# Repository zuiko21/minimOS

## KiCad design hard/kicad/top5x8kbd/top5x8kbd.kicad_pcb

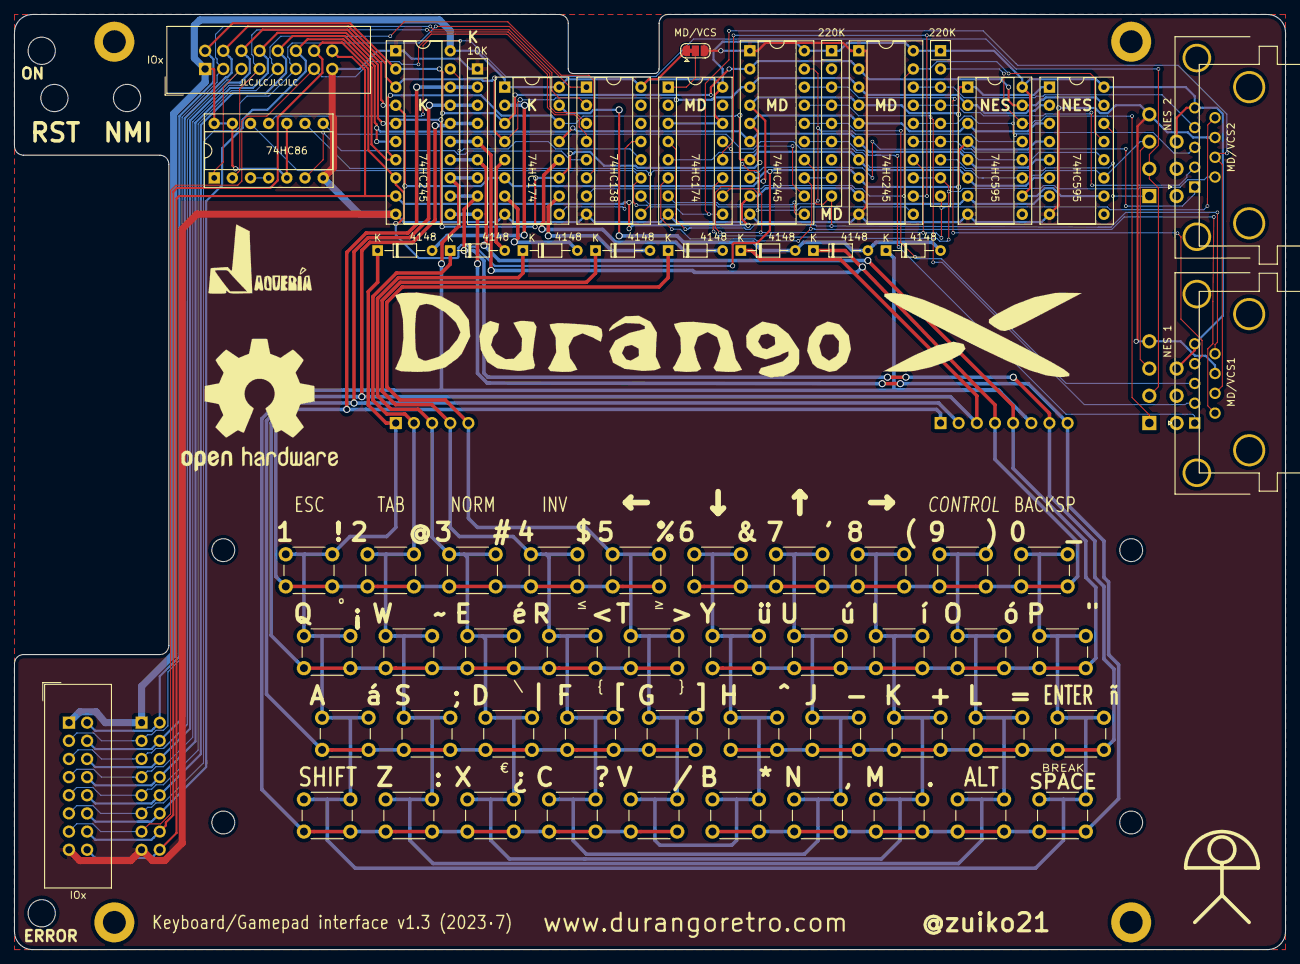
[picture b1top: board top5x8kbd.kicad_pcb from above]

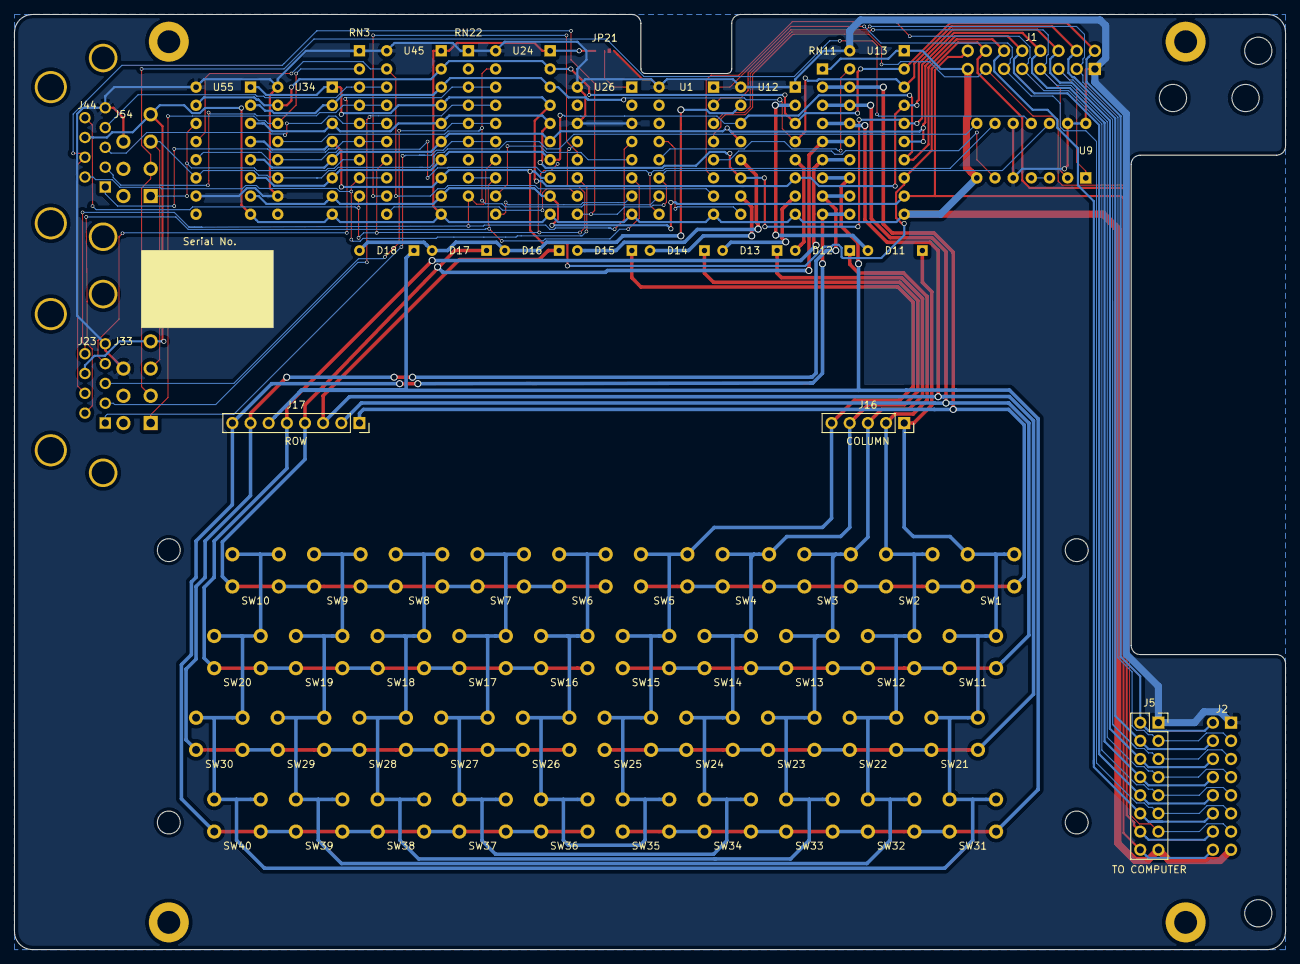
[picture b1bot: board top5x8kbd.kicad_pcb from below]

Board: 2 copper layers, 177.8 x 130.8 mm, 81 parts (3 on the bottom side), 64 nets.

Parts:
D11, D12, D13, D14, D15, D16, D17, D18: 4148; D_DO-34_SOD68_P7.62mm_Horizontal
H1: RST; MountingHole_3.2mm_M3_DIN965_Pad
H2: NMI; MountingHole_3.2mm_M3_DIN965_Pad
H3, H4: MountingHole_3.2mm_M3_DIN965_Pad
H5, H6, H7, H8: MountingHole_3.2mm_M3_DIN965
J1, J2: IOx; IDC-Header_2x08_P2.54mm_Vertical
J5: TO COMPUTER; PinSocket_2x08_P2.54mm_Vertical
J16: COLUMN; PinSocket_1x05_P2.54mm_Vertical
J17: ROW; PinSocket_1x08_P2.54mm_Vertical
J23: MD/VCS1; DSUB-9_Male_Horizontal_P2.77x2.84mm_EdgePinOffset4.94mm_Hou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
J33: NES 1; NES gamepad
J44: MD/VCS2; DSUB-9_Male_Horizontal_P2.77x2.84mm_EdgePinOffset4.94mm_Hou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
J54: NES 2; NES gamepad
JP21: MD/VCS; SolderJumper-3_P1.3mm_Bridged12_RoundedPad1.0x1.5mm
LOGO1: OSHW-Logo2_24.3x20mm_SilkScreen
LOGO2: durango-x18
LOGO3: jaqueria
RN3, RN22: 220K; R_Array_SIP9
RN11: 10K; R_Array_SIP9
SW1: 1 !; SW_PUSH_6mm
SW2: 2 @; SW_PUSH_6mm
SW3: 3 #; SW_PUSH_6mm
SW4: 4 $; SW_PUSH_6mm
SW5: 5 %; SW_PUSH_6mm
SW6: 6 &; SW_PUSH_6mm
SW7: 7 '; SW_PUSH_6mm
SW8: 8 (; SW_PUSH_6mm
SW9: 9 ); SW_PUSH_6mm
SW10: 0 _; SW_PUSH_6mm
SW11: Q ¡; SW_PUSH_6mm
SW12: W ~~; SW_PUSH_6mm
SW13: E é; SW_PUSH_6mm
SW14: R <; SW_PUSH_6mm
SW15: T >; SW_PUSH_6mm
SW16: Y ü; SW_PUSH_6mm
SW17: U ú; SW_PUSH_6mm
SW18: I í; SW_PUSH_6mm
SW19: O ó; SW_PUSH_6mm
SW20: P "; SW_PUSH_6mm
SW21: A á; SW_PUSH_6mm
SW22: S ;; SW_PUSH_6mm
SW23: D |; SW_PUSH_6mm
SW24: F [; SW_PUSH_6mm
SW25: G ]; SW_PUSH_6mm
SW26: H ^; SW_PUSH_6mm
SW27: J -; SW_PUSH_6mm
SW28: K +; SW_PUSH_6mm
SW29: L =; SW_PUSH_6mm
SW30: ENTER ñ; SW_PUSH_6mm
SW31: SHIFT; SW_PUSH_6mm
SW32: Z :; SW_PUSH_6mm
SW33: X ¿; SW_PUSH_6mm
SW34: C ?; SW_PUSH_6mm
SW35: V /; SW_PUSH_6mm
SW36: B *; SW_PUSH_6mm
SW37: N ,; SW_PUSH_6mm
SW38: M .; SW_PUSH_6mm
SW39: ALT; SW_PUSH_6mm
SW40: SPACE; SW_PUSH_6mm
U1: 74HC138; DIP-16_W7.62mm_Socket
U9: 74HC86; DIP-14_W7.62mm_Socket
U12, U26: 74HC174; DIP-16_W7.62mm_Socket
U13, U24, U45: 74HC245; DIP-20_W7.62mm_Socket
U34, U55: 74HC595; DIP-16_W7.62mm_Socket

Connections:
+5V: J1.1, J2.1, J5.1, J23.5, J33.6, J44.5, J54.6, JP21.1, RN3.1, RN22.1, U1.16, U9.5, U9.10, U9.13, U9.14, U12.1, U12.16, U13.20, U24.20, U26.3, U26.14, U26.16, U34.10, U34.16, U45.20, U55.10, U55.16
/BR~W: J1.11, J2.11, J5.11, U1.1
/C1: D11.2, U12.2
/C2: D12.2, U12.5
/C3: D13.2, U12.7
/C4: D14.2, U12.10
/C5: D15.2, U12.12
/ID: D16.2, D17.2, D18.2, U12.15
/K~OE: U1.12, U13.19
/LATCH: J33.3, J54.3, U9.11
/NCLK: J33.5, J54.5, U9.8, U34.11, U55.11
/P1~OE: U1.10, U24.19, U34.13
/P2~OE: U1.7, U45.19, U55.13
/SEL: U9.3, U9.4
/VCS: JP21.2, U26.1
/~A1: U24.11, U26.7
/~A2: U26.10, U45.11
/~AB1: J23.6, RN22.8, U24.13, U26.6
/~AB2: J44.6, RN3.8, U26.11, U45.13
/~CSEL: U1.13, U12.9
/~DAT1: J33.1, RN3.2, U34.14
/~DAT2: J54.1, RN3.7, U55.14
/~DN1: J23.2, RN22.4, U24.17
/~DN2: J44.2, RN3.4, U45.17
/~IOX: J1.13, J2.13, J5.13, U1.4
/~LATCH: J23.7, J44.7, U1.11, U9.12, U26.9
/~LT1: J23.3, RN22.5, U24.16
/~LT2: J44.3, RN3.5, U45.16
/~NCLK: U1.9, U9.9, U34.12, U55.12
/~RT1: J23.4, RN22.3, U24.18
/~RT2: J44.4, RN3.3, U45.18
/~S1: U24.12, U26.5
/~S2: U26.12, U45.12
/~SC1: J23.9, RN22.9, U24.14, U26.4
/~SC2: J44.9, RN3.9, U26.13, U45.14
/~SEL: U1.5, U9.6
/~UP1: J23.1, RN22.6, U24.15
/~UP2: J44.1, RN3.6, U45.15
BA0: J1.3, J2.3, J5.3, U1.2
BA1: J1.5, J2.5, J5.5, U9.1
BA2: J1.7, J2.7, J5.7, U1.3, U9.2
BA3: J1.9, J2.9, J5.9, U1.6
COL1: D11.1, J16.1, SW1.2, SW10.2, SW11.2, SW20.2, SW21.2, SW30.2, SW31.2, SW40.2
COL2: D12.1, J16.2, SW2.2, SW9.2, SW12.2, SW19.2, SW22.2, SW29.2, SW32.2, SW39.2
COL3: D13.1, J16.3, SW3.2, SW8.2, SW13.2, SW18.2, SW23.2, SW28.2, SW33.2, SW38.2
COL4: D14.1, J16.4, SW4.2, SW7.2, SW14.2, SW17.2, SW24.2, SW27.2, SW34.2, SW37.2
COL5: D15.1, J16.5, SW5.2, SW6.2, SW15.2, SW16.2, SW25.2, SW26.2, SW35.2, SW36.2
GND: J1.15, J2.15, J5.15, J23.8, J33.7, J44.8, J54.7, JP21.3, RN11.1, U1.8, U9.7, U12.8, U13.1, U13.10, U24.1, U24.10, U26.8, U34.8, U45.1, U45.10, U55.8
PD0: J1.2, J2.2, J5.2, U12.3, U13.2, U24.2, U34.15, U45.2, U55.15
PD1: J1.4, J2.4, J5.4, U12.4, U13.3, U24.3, U34.2, U45.3, U55.2
PD2: J1.6, J2.6, J5.6, U12.6, U13.4, U24.4, U34.1, U45.4, U55.1
PD3: J1.8, J2.8, J5.8, U12.11, U13.5, U24.5, U34.3, U45.5, U55.3
PD4: J1.10, J2.10, J5.10, U12.13, U13.6, U24.6, U34.5, U45.6, U55.5
PD5: J1.12, J2.12, J5.12, U12.14, U13.7, U24.7, U34.6, U45.7, U55.6
PD6: J1.14, J2.14, J5.14, U13.8, U24.8, U34.4, U45.8, U55.4
PD7: J1.16, J2.16, J5.16, U13.9, U24.9, U34.7, U45.9, U55.7
ROW1: J17.1, RN11.2, SW1.1, SW2.1, SW3.1, SW4.1, SW5.1, U13.18
ROW2: J17.2, RN11.3, SW11.1, SW12.1, SW13.1, SW14.1, SW15.1, U13.17
ROW3: D16.1, J17.3, RN11.4, SW21.1, SW22.1, SW23.1, SW24.1, SW25.1, U13.16
ROW4: D17.1, J17.4, RN11.5, SW6.1, SW7.1, SW8.1, SW9.1, SW10.1, U13.15
ROW5: J17.5, RN11.6, SW16.1, SW17.1, SW18.1, SW19.1, SW20.1, U13.14
ROW6: D18.1, J17.6, RN11.7, SW31.1, SW32.1, SW33.1, SW34.1, SW35.1, U13.13
ROW7: J17.7, RN11.8, SW26.1, SW27.1, SW28.1, SW29.1, SW30.1, U13.12
ROW8: J17.8, RN11.9, SW36.1, SW37.1, SW38.1, SW39.1, SW40.1, U13.11

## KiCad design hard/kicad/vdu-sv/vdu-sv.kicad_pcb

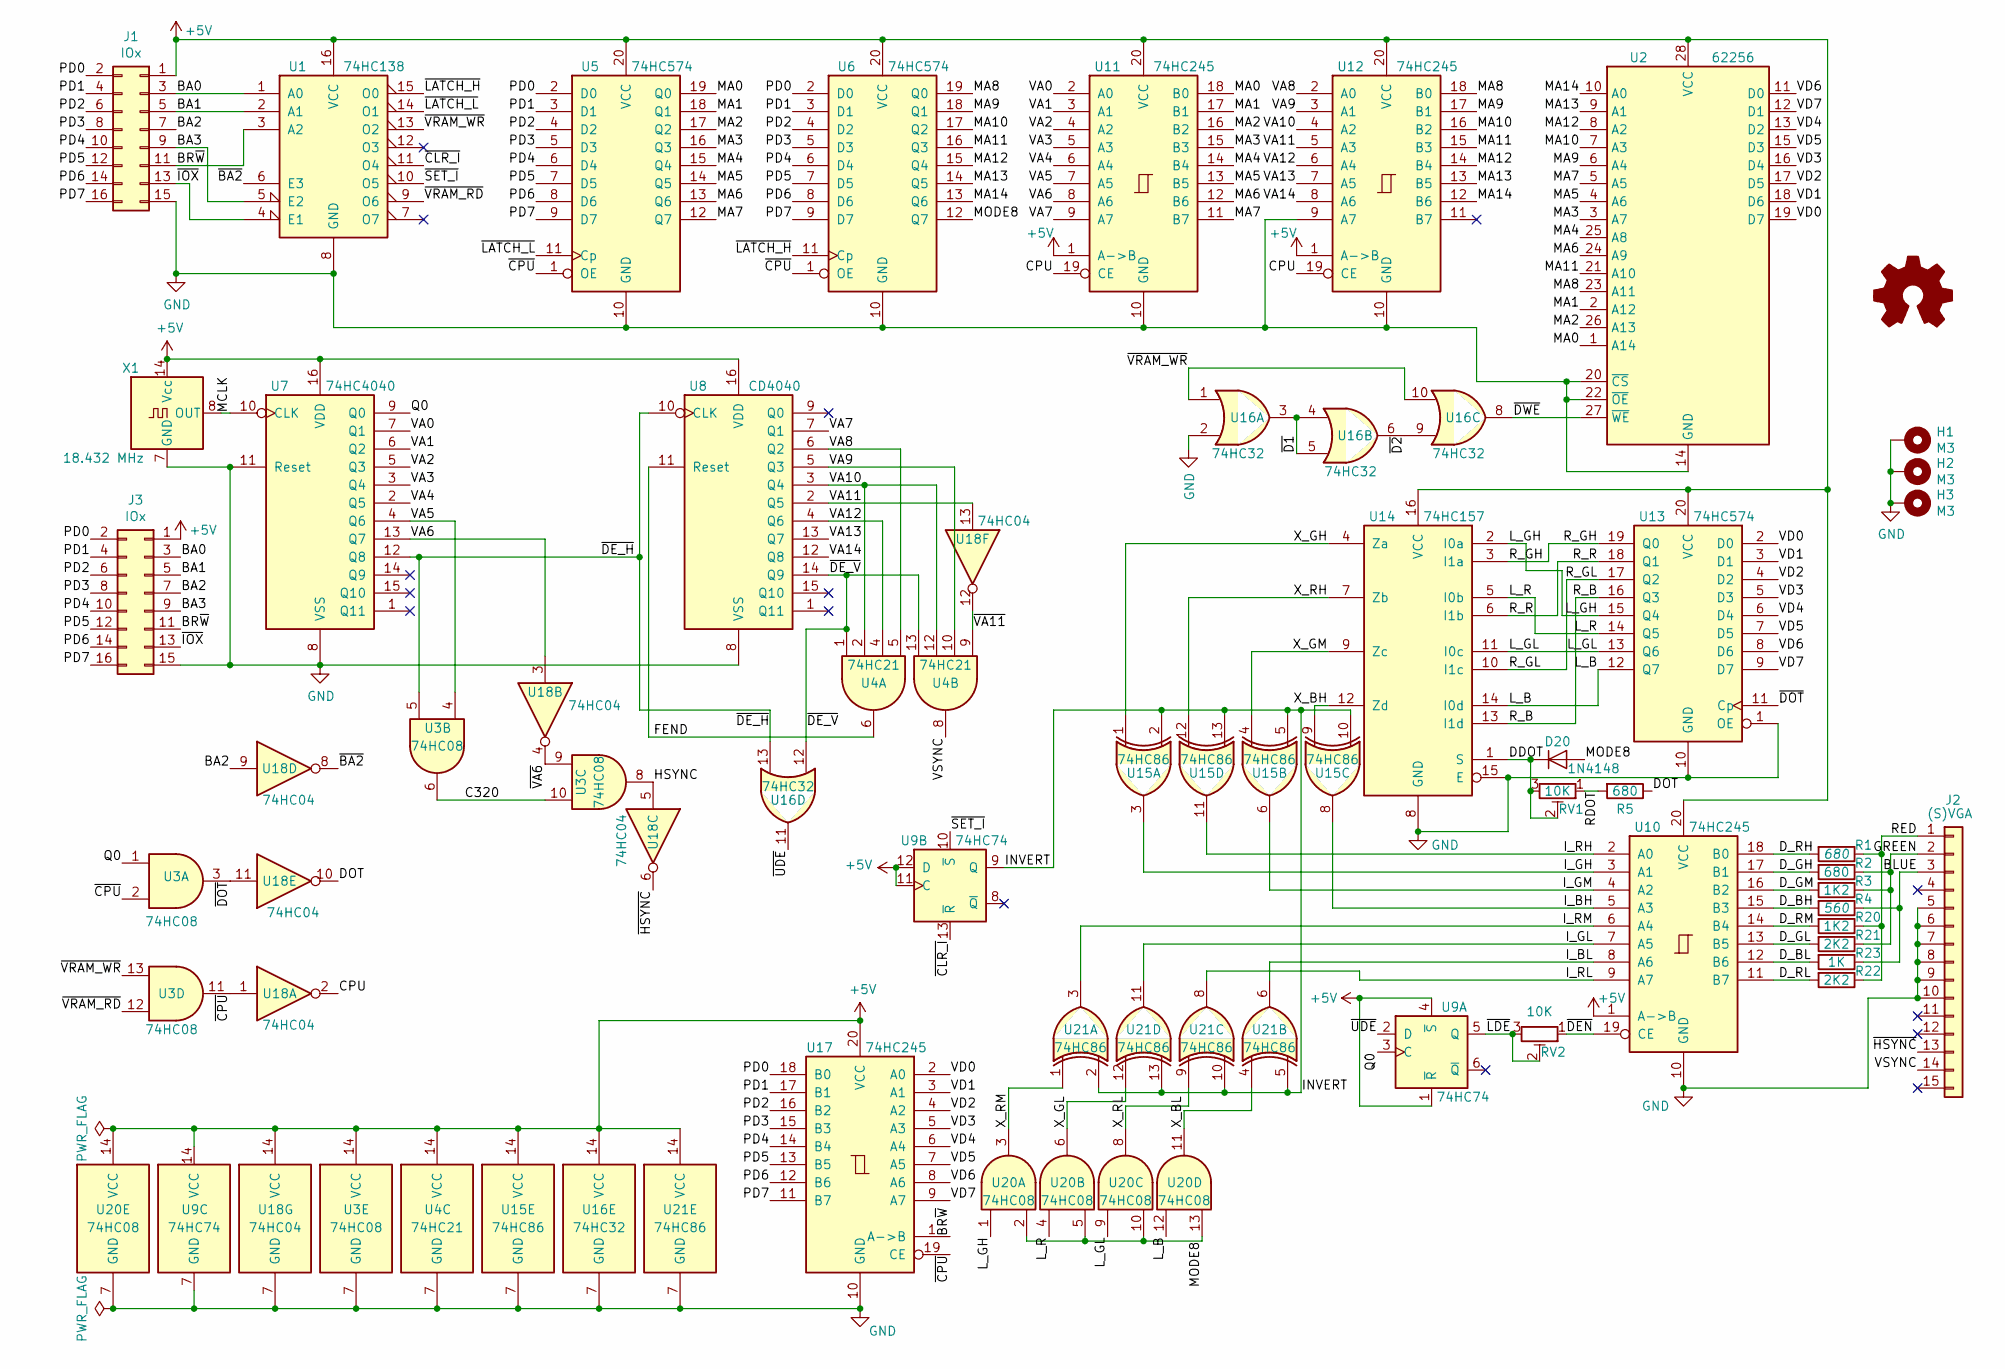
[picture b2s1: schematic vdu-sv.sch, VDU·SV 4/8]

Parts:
D20: 1N4148; D_DO-35_SOD27_P2.54mm_Vertical_AnodeUp
H1, H2, H3: M3; MountingHole_3.2mm_M3_DIN965_Pad
J1: IOx; PinSocket_2x08_P2.54mm_Horizontal
J2: (S)VGA; DSUB-15-HD_Female_Horizontal_P2.29x1.98mm_EdgePinOffset3.03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
J3: IOx; IDC-Header_2x08_P2.54mm_Vertical
LOGO1: La Jaquería; jaqueria
R1, R2, R5: 680; R_Axial_DIN0207_L6.3mm_D2.5mm_P2.54mm_Vertical
R3, R20: 1K2; R_Axial_DIN0207_L6.3mm_D2.5mm_P2.54mm_Vertical
R4: 560; R_Axial_DIN0207_L6.3mm_D2.5mm_P2.54mm_Vertical
R21, R22: 2K2; R_Axial_DIN0207_L6.3mm_D2.5mm_P2.54mm_Vertical
R23: 1K; R_Axial_DIN0207_L6.3mm_D2.5mm_P2.54mm_Vertical
RV1, RV2: 10K; Potentiometer_Piher_PT-6-V_Vertical
U1: 74HC138; DIP-16_W7.62mm_Socket
U2: 62256; DIP-28_W7.62mm_Socket
U3, U20: 74HC08; DIP-14_W7.62mm_Socket
U4: 74HC21; DIP-14_W7.62mm_Socket
U5, U6, U13: 74HC574; DIP-20_W7.62mm_Socket
U7: 74HC4040; DIP-16_W7.62mm_Socket
U8: CD4040; DIP-16_W7.62mm_Socket
U9: 74HC74; DIP-14_W7.62mm_Socket
U10, U11, U12, U17: 74HC245; DIP-20_W7.62mm_Socket
U14: 74HC157; DIP-16_W7.62mm_Socket
U15, U21: 74HC86; DIP-14_W7.62mm_Socket
U16: 74HC32; DIP-14_W7.62mm_Socket
U18: 74HC04; DIP-14_W7.62mm_Socket
X1: 18.432 MHz; Oscillator_DIP-14

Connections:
+5V: J1.1, J3.1, U1.16 (VCC), U2.28 (VCC), U3.14 (VCC), U4.14 (VCC), U5.20 (VCC), U6.20 (VCC), U7.16 (VDD), U8.16 (VDD), U9.1 (~R), U9.4 (~S), U9.11 (C), U9.12 (D), U9.14 (VCC), U10.1 (A->B), U10.20 (VCC), U11.1 (A->B), U11.20 (VCC), U12.1 (A->B), U12.20 (VCC), U13.20 (VCC), U14.16 (VCC), U15.14 (VCC), U16.14 (VCC), U17.20 (VCC), U18.14 (VCC), U20.14 (VCC), U21.14 (VCC), X1.14 (Vcc)
/BA0: J1.3, J3.3, U1.1 (A0)
/BA1: J1.5, J3.5, U1.2 (A1)
/BA2: J1.7, J3.7, U18.9
/BA3: J1.9, J3.9, U1.5 (E2)
/BLUE: J2.3, R4.1, R23.1
/BR~W: J1.11, J3.11, U1.3 (A2), U17.1 (A->B)
/C320: U3.6, U3.10
/CPU: U11.19 (CE), U12.19 (CE), U18.2
/DDOT: D20.1 (K), RV1.2, RV1.3, U14.1 (S)
/DOT: R5.1, U18.10
/D_BH: R4.2, U10.15 (B3)
/D_BL: R23.2, U10.12 (B6)
/D_GH: R2.2, U10.17 (B1)
/D_GL: R21.2, U10.13 (B5)
/D_GM: R3.2, U10.16 (B2)
/D_RH: R1.2, U10.18 (B0)
/D_RL: R22.2, U10.11 (B7)
/D_RM: R20.2, U10.14 (B4)
/FEND: U4.6, U8.11 (Reset)
/GREEN: J2.2, R2.1, R3.1, R21.1
/HSYNC: U3.8, U18.5
/INVERT: U9.9 (Q), U15.2, U15.5, U15.10, U15.13, U21.2, U21.5, U21.10, U21.13
/I_BH: U10.5 (A3), U15.8
/I_BL: U10.8 (A6), U21.6
/I_GH: U10.3 (A1), U15.3
/I_GL: U10.7 (A5), U21.11
/I_GM: U10.4 (A2), U15.6
/I_RH: U10.2 (A0), U15.11
/I_RL: U10.9 (A7), U21.8
/I_RM: U10.6 (A4), U21.3
/L_B: U13.12 (Q7), U14.14 (I0d), U20.12
/L_GH: U13.15 (Q4), U14.2 (I0a), U20.1
/L_GL: U13.13 (Q6), U14.11 (I0c), U20.9
/L_R: U13.14 (Q5), U14.5 (I0b), U20.4
/MA0: U2.1 (A14), U5.19 (Q0), U11.18 (B0)
/MA1: U2.2 (A12), U5.18 (Q1), U11.17 (B1)
/MA2: U2.26 (A13), U5.17 (Q2), U11.16 (B2)
/MA3: U2.3 (A7), U5.16 (Q3), U11.15 (B3)
/MA4: U2.25 (A8), U5.15 (Q4), U11.14 (B4)
/MA5: U2.4 (A6), U5.14 (Q5), U11.13 (B5)
/MA6: U2.24 (A9), U5.13 (Q6), U11.12 (B6)
/MA7: U2.5 (A5), U5.12 (Q7), U11.11 (B7)
/MA8: U2.23 (A11), U6.19 (Q0), U12.18 (B0)
/MA9: U2.6 (A4), U6.18 (Q1), U12.17 (B1)
/MA10: U2.7 (A3), U6.17 (Q2), U12.16 (B2)
/MA11: U2.21 (A10), U6.16 (Q3), U12.15 (B3)
/MA12: U2.8 (A2), U6.15 (Q4), U12.14 (B4)
/MA13: U2.9 (A1), U6.14 (Q5), U12.13 (B5)
/MA14: U2.10 (A0), U6.13 (Q6), U12.12 (B6)
/MCLK: U7.10 (CLK), X1.8 (OUT)
/MODE8: D20.2 (A), U6.12 (Q7), U20.2, U20.5, U20.10, U20.13
/PD0: J1.2, J3.2, U5.2 (D0), U6.2 (D0), U17.18 (B0)
/PD1: J1.4, J3.4, U5.3 (D1), U6.3 (D1), U17.17 (B1)
/PD2: J1.6, J3.6, U5.4 (D2), U6.4 (D2), U17.16 (B2)
/PD3: J1.8, J3.8, U5.5 (D3), U6.5 (D3), U17.15 (B3)
/PD4: J1.10, J3.10, U5.6 (D4), U6.6 (D4), U17.14 (B4)
/PD5: J1.12, J3.12, U5.7 (D5), U6.7 (D5), U17.13 (B5)
/PD6: J1.14, J3.14, U5.8 (D6), U6.8 (D6), U17.12 (B6)
/PD7: J1.16, J3.16, U5.9 (D7), U6.9 (D7), U17.11 (B7)
/Q0: U3.1, U7.9 (Q0), U9.3 (C)
/RDOT: R5.2, RV1.1
/RED: J2.1, R1.1, R20.1, R22.1
/R_B: U13.16 (Q3), U14.13 (I1d)
/R_GH: U13.19 (Q0), U14.3 (I1a)
/R_GL: U13.17 (Q2), U14.10 (I1c)
/R_R: U13.18 (Q1), U14.6 (I1b)
/VA0: U7.7 (Q1), U11.2 (A0)
/VA1: U7.6 (Q2), U11.3 (A1)
/VA2: U7.5 (Q3), U11.4 (A2)
/VA3: U7.3 (Q4), U11.5 (A3)
/VA4: U7.2 (Q5), U11.6 (A4)
/VA5: U3.4, U7.4 (Q6), U11.7 (A5)
/VA6: U7.13 (Q7), U11.8 (A6), U18.3
/VA7: U8.7 (Q1), U11.9 (A7)
/VA8: U4.5, U8.6 (Q2), U12.2 (A0)
/VA9: U4.10, U8.5 (Q3), U12.3 (A1)
/VA10: U4.2, U4.12, U8.3 (Q4), U12.4 (A2)
/VA11: U8.2 (Q5), U12.5 (A3), U18.13
/VA12: U4.4, U8.4 (Q6), U12.6 (A4)
/VA13: U8.13 (Q7), U12.7 (A5)
/VA14: U8.12 (Q8), U12.8 (A6)
/VD0: U2.19 (D7), U13.2 (D0), U17.2 (A0)
/VD1: U2.18 (D6), U13.3 (D1), U17.3 (A1)
/VD2: U2.17 (D5), U13.4 (D2), U17.4 (A2)
/VD3: U2.16 (D4), U13.5 (D3), U17.5 (A3)
/VD4: U2.13 (D2), U13.6 (D4), U17.6 (A4)
/VD5: U2.15 (D3), U13.7 (D5), U17.7 (A5)
/VD6: U2.11 (D0), U13.8 (D6), U17.8 (A6)
/VD7: U2.12 (D1), U13.9 (D7), U17.9 (A7)
/VSYNC: J2.14, U4.8
/X_BH: U14.12 (Zd), U15.9
/X_BL: U20.11, U21.4
/X_GH: U14.4 (Za), U15.1
/X_GL: U20.6, U21.12
/X_GM: U14.9 (Zc), U15.4
/X_RH: U14.7 (Zb), U15.12
/X_RL: U20.8, U21.9
/X_RM: U20.3, U21.1
/~BA2: U1.6 (E3), U18.8
/~CLR_I: U1.11 (O4), U9.13 (~R)
/~CPU: U3.2, U3.11, U5.1 (OE), U6.1 (OE), U17.19 (CE), U18.1
/~D1: U16.3, U16.4, U16.5
/~D2: U16.6, U16.9
/~DEN: RV2.1, U10.19 (CE)
/~DE_H: U3.5, U7.12 (Q8), U8.10 (CLK), U16.13
/~DE_V: U4.1, U4.13, U8.14 (Q9), U16.12
/~DOT: U3.3, U13.11 (Cp), U18.11
/~DWE: U2.27 (~WE~), U16.8
/~HSYNC: J2.13, U18.6
/~IOX: J1.13, J3.13, U1.4 (E1)
/~LATCH_H: U1.15 (O0), U6.11 (Cp)
/~LATCH_L: U1.14 (O1), U5.11 (Cp)
/~LDE: RV2.2, RV2.3, U9.5 (Q)
/~SET_I: U1.10 (O5), U9.10 (~S)
/~UDE: U9.2 (D), U16.11
/~VA6: U3.9, U18.4
/~VA11: U4.9, U18.12
/~VRAM_RD: U1.9 (O6), U3.12
/~VRAM_WR: U1.13 (O2), U3.13, U16.1, U16.10
GND: H1.1, H2.1, H3.1, J1.15, J2.5, J2.6, J2.7, J2.8, J2.9, J2.10, J3.15, U1.8 (GND), U2.14 (GND), U2.20 (~CS), U2.22 (~OE~), U3.7 (GND), U4.7 (GND), U5.10 (GND), U6.10 (GND), U7.8 (VSS), U7.11 (Reset), U8.8 (VSS), U9.7 (GND), U10.10 (GND), U11.10 (GND), U12.9 (A7), U12.10 (GND), U13.1 (OE), U13.10 (GND), U14.8 (GND), U14.15 (E), U15.7 (GND), U16.2, U16.7 (GND), U17.10 (GND), U18.7 (GND), U20.7 (GND), U21.7 (GND), X1.7 (GND)

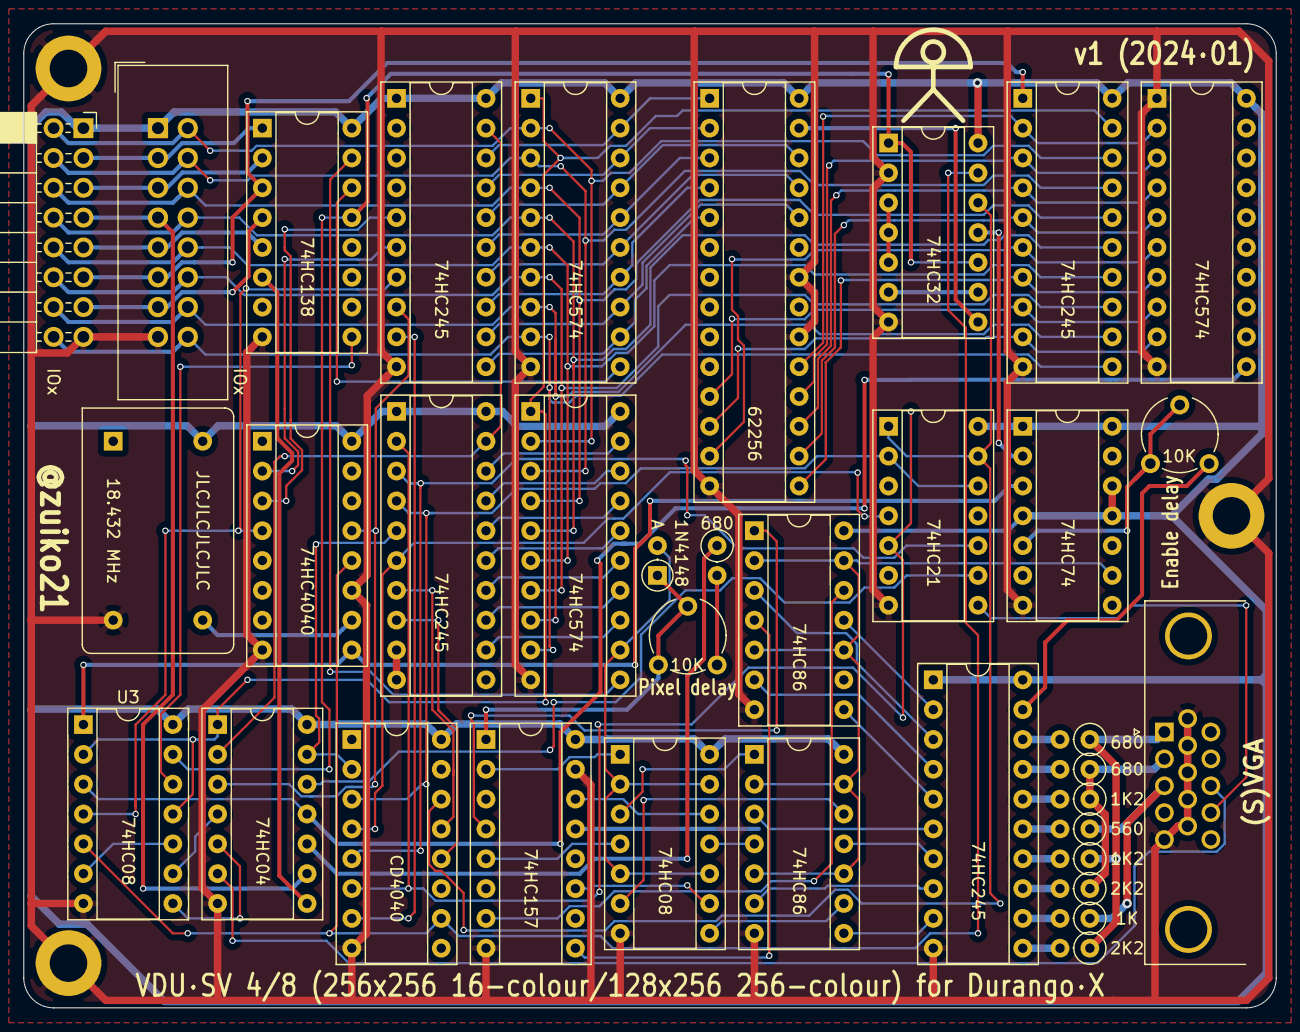
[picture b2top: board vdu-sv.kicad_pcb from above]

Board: 2 copper layers, 106.7 x 83.8 mm, 40 parts (1 on the bottom side), 121 nets.

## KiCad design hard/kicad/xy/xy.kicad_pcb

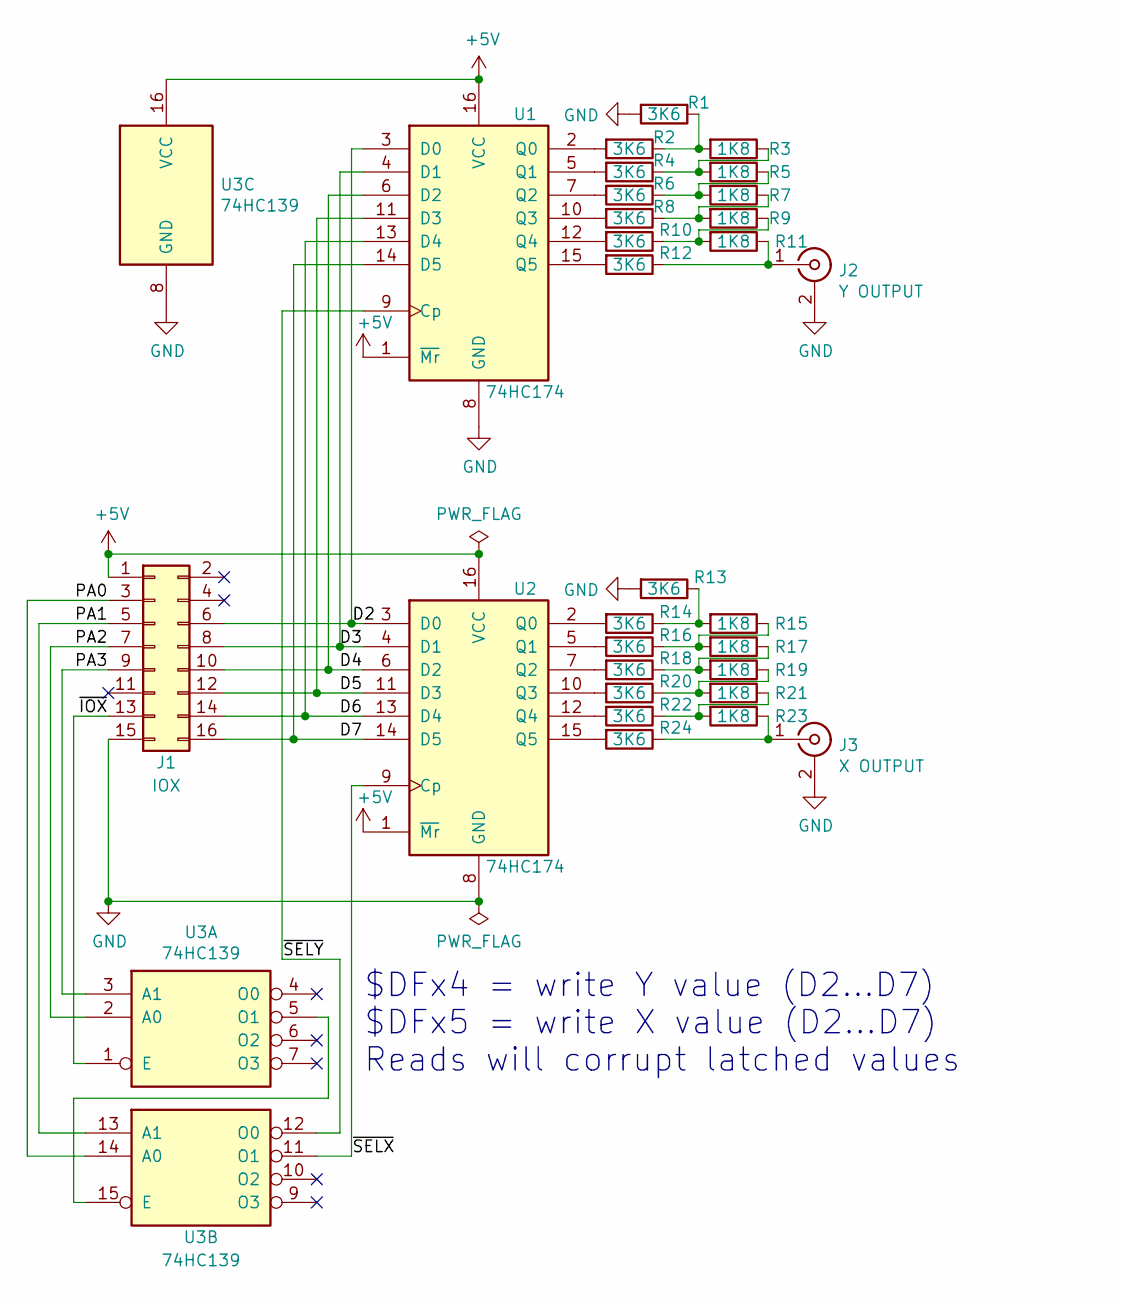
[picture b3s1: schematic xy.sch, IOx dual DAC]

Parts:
J1: IOX; IDC-Header_2x08_P2.54mm_Vertical
J2: Y OUTPUT; PinHeader_1x02_P2.54mm_Vertical
J3: X OUTPUT; PinHeader_1x02_P2.54mm_Vertical
R1, R2, R4, R6, R8, R10, R12, R13, R14, R16, R18, R20, R22, R24: 3K6; R_Axial_DIN0207_L6.3mm_D2.5mm_P2.54mm_Vertical
R3, R5, R7, R9, R11, R15, R17, R19, R21, R23: 1K8; R_Axial_DIN0207_L6.3mm_D2.5mm_P2.54mm_Vertical
U1, U2: 74HC174; DIP-16_W7.62mm_Socket
U3: 74HC139; DIP-16_W7.62mm_Socket

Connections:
+5V: J1.1, U1.1 (~Mr), U1.16 (VCC), U2.1 (~Mr), U2.16 (VCC), U3.16 (VCC)
/D2: J1.6, U1.3 (D0), U2.3 (D0)
/D3: J1.8, U1.4 (D1), U2.4 (D1)
/D4: J1.10, U1.6 (D2), U2.6 (D2)
/D5: J1.12, U1.11 (D3), U2.11 (D3)
/D6: J1.14, U1.13 (D4), U2.13 (D4)
/D7: J1.16, U1.14 (D5), U2.14 (D5)
/PA0: J1.3, U3.14 (A0)
/PA1: J1.5, U3.13 (A1)
/PA2: J1.7, U3.2 (A0)
/PA3: J1.9, U3.3 (A1)
/~IOX: J1.13, U3.1 (E)
/~SELX: U2.9 (Cp), U3.11 (O1)
/~SELY: U1.9 (Cp), U3.12 (O0)
GND: J1.15, J2.2 (Ext), J3.2 (Ext), R1.2, R13.2, U1.8 (GND), U2.8 (GND), U3.8 (GND)
unnamed: J2.1 (In), R11.1, R12.1
unnamed: J3.1 (In), R23.1, R24.1
unnamed: R1.1, R2.1, R3.2
unnamed: R2.2, U1.2 (Q0)
unnamed: R3.1, R4.1, R5.2
unnamed: R4.2, U1.5 (Q1)
unnamed: R5.1, R6.1, R7.2
unnamed: R6.2, U1.7 (Q2)
unnamed: R7.1, R8.1, R9.2
unnamed: R8.2, U1.10 (Q3)
unnamed: R9.1, R10.1, R11.2
unnamed: R10.2, U1.12 (Q4)
unnamed: R12.2, U1.15 (Q5)
unnamed: R13.1, R14.1, R15.2
unnamed: R14.2, U2.2 (Q0)
unnamed: R15.1, R16.1, R17.2
unnamed: R16.2, U2.5 (Q1)
unnamed: R17.1, R18.1, R19.2
unnamed: R18.2, U2.7 (Q2)
unnamed: R19.1, R20.1, R21.2
unnamed: R20.2, U2.10 (Q3)
unnamed: R21.1, R22.1, R23.2
unnamed: R22.2, U2.12 (Q4)
unnamed: R24.2, U2.15 (Q5)
unnamed: U3.5 (O1), U3.15 (E)

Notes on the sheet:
$DFx4 = write Y value (D2…D7) $DFx5 = write X value (D2…D7) Reads will corrupt latched values

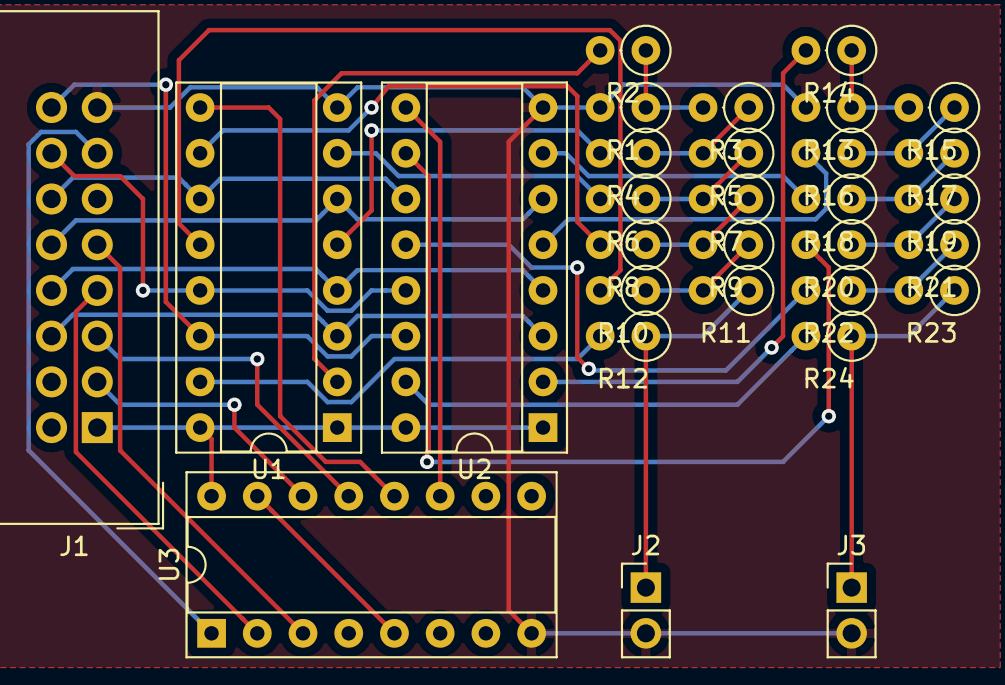
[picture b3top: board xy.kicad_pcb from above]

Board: 2 copper layers, 30 parts (0 on the bottom side), 40 nets.

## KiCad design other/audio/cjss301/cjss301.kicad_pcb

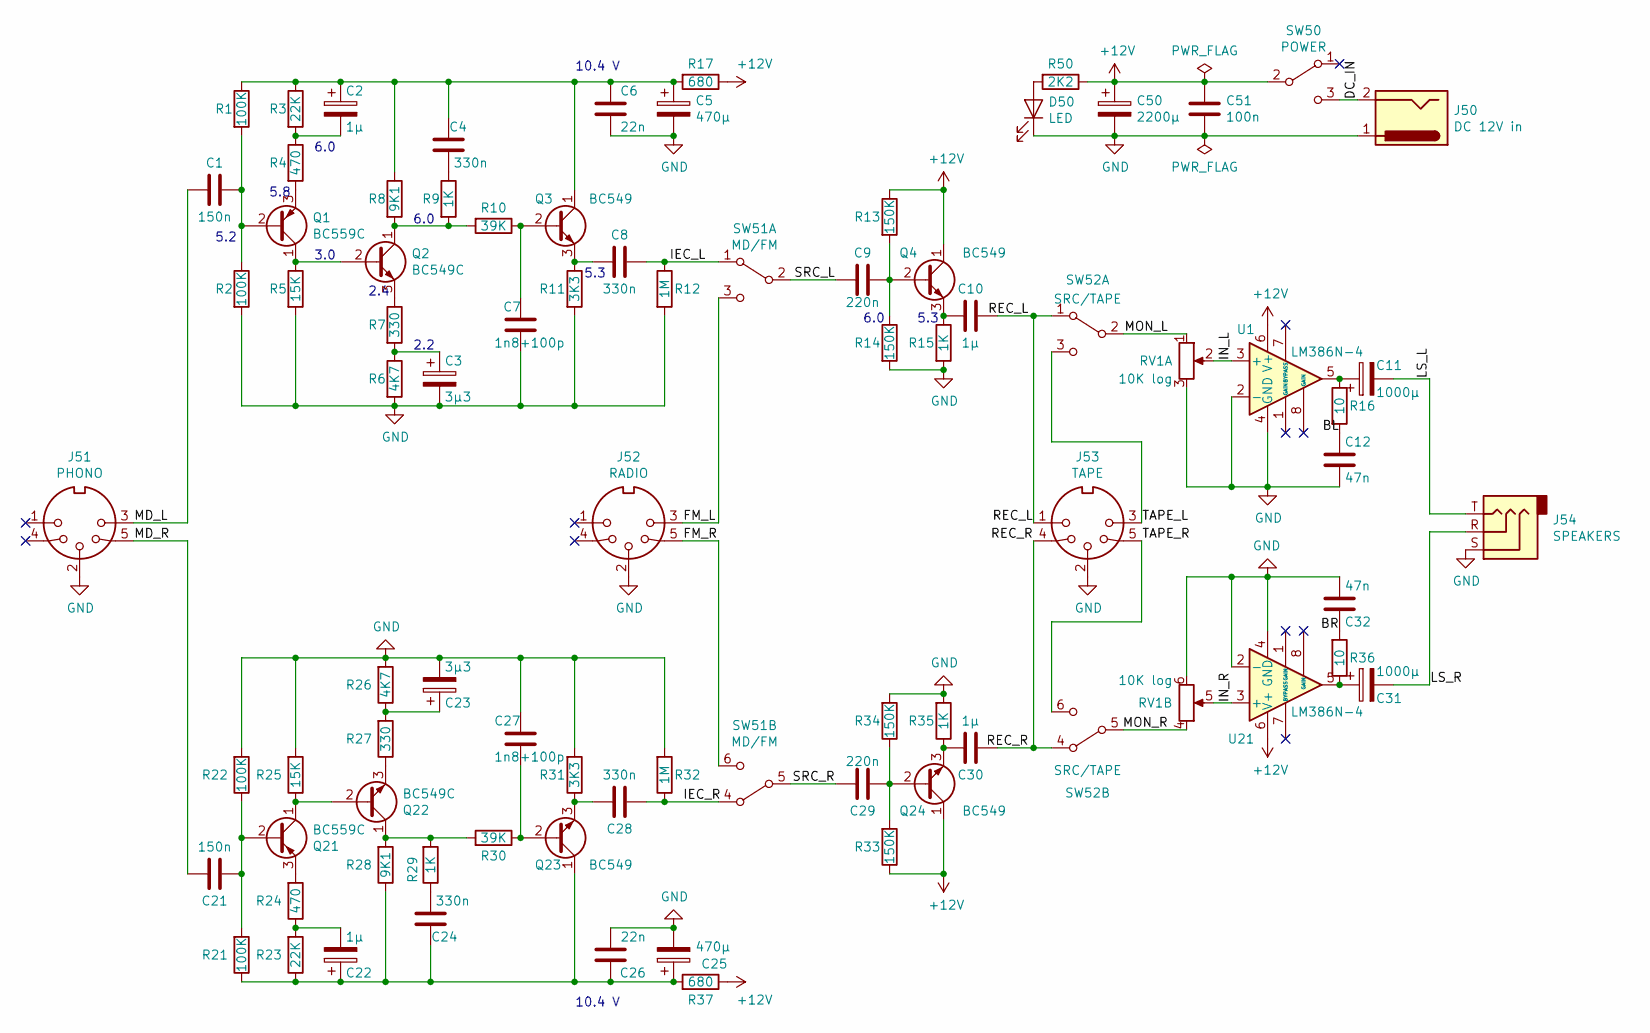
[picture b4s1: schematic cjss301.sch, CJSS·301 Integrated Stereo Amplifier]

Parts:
C1, C21: 150n; C_Rect_L11.0mm_W5.1mm_P10.00mm_MKT
C2, C22: 1µ; CP_Radial_D4.0mm_P2.00mm
C3, C23: 3µ3; CP_Radial_D5.0mm_P2.00mm
C4, C8, C24, C28: 330n; C_Rect_L11.0mm_W6.3mm_P10.00mm_MKT
C5, C25: 470µ; CP_Radial_D8.0mm_P3.50mm
C6, C26: 22n; C_Disc_D6.0mm_W2.5mm_P5.00mm
C7, C27: 1n8+100p; C_Axial_L12.0mm_D6.5mm_P15.00mm_Horizontal
C9, C29: 220n; C_Rect_L11.0mm_W4.3mm_P10.00mm_MKT
C10, C30: 1µ; C_Rect_L16.5mm_W4.7mm_P15.00mm_MKT
C11, C31: 1000µ; CP_Radial_D10.0mm_P5.00mm
C12, C32: 47n; C_Rect_L11.0mm_W2.8mm_P10.00mm_MKT
C50: 2200µ; CP_Radial_D13.0mm_P5.00mm
C51: 100n; C_Rect_L7.0mm_W2.0mm_P5.00mm
D50: LED; LED_D3.0mm
J50: DC 12V in; BarrelJack_CUI_PJ-102AH_Horizontal
J51: PHONO; PinHeader_1x05_P2.54mm_Vertical
J52: RADIO; PinHeader_1x05_P2.54mm_Vertical
J53: TAPE; PinHeader_1x05_P2.54mm_Vertical
J54: SPEAKERS; Jack_3.5mm_CUI_SJ1-3533NG_Horizontal
Q1, Q21: BC559C; TO-92_Inline
Q2, Q22: BC549C; TO-92_Inline
Q3, Q4, Q23, Q24: BC549; TO-92_Inline
R1, R2, R21, R22: 100K; R_Axial_DIN0207_L6.3mm_D2.5mm_P10.16mm_Horizontal
R3, R23: 22K; R_Axial_DIN0207_L6.3mm_D2.5mm_P10.16mm_Horizontal
R4, R24: 470; R_Axial_DIN0207_L6.3mm_D2.5mm_P10.16mm_Horizontal
R5, R25: 15K; R_Axial_DIN0207_L6.3mm_D2.5mm_P10.16mm_Horizontal
R6, R26: 4K7; R_Axial_DIN0207_L6.3mm_D2.5mm_P10.16mm_Horizontal
R7, R27: 330; R_Axial_DIN0207_L6.3mm_D2.5mm_P10.16mm_Horizontal
R8, R28: 9K1; R_Axial_DIN0207_L6.3mm_D2.5mm_P10.16mm_Horizontal
R9, R15, R29, R35: 1K; R_Axial_DIN0207_L6.3mm_D2.5mm_P10.16mm_Horizontal
R10, R30: 39K; R_Axial_DIN0207_L6.3mm_D2.5mm_P10.16mm_Horizontal
R11, R31: 3K3; R_Axial_DIN0207_L6.3mm_D2.5mm_P10.16mm_Horizontal
R12, R32: 1M; R_Axial_DIN0207_L6.3mm_D2.5mm_P10.16mm_Horizontal
R13, R14, R33, R34: 150K; R_Axial_DIN0207_L6.3mm_D2.5mm_P10.16mm_Horizontal
R16, R36: 10; R_Axial_DIN0207_L6.3mm_D2.5mm_P10.16mm_Horizontal
R17, R37: 680; R_Axial_DIN0207_L6.3mm_D2.5mm_P10.16mm_Horizontal
R50: 2K2; R_Axial_DIN0207_L6.3mm_D2.5mm_P10.16mm_Horizontal
RV1: 10K log; PinHeader_2x03_StereoPot
SW50: POWER; PinHeader_1x03_P2.54mm_Vertical
SW51: MD/FM; PinHeader_2x03_StereoPot
SW52: SRC/TAPE; PinHeader_2x03_StereoPot
U1, U21: LM386N-4; DIP-8_W7.62mm

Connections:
+12V: C50.1, C51.1, Q4.1 (C), Q24.1 (C), R13.1, R17.1, R33.1, R37.1, R50.1, SW50.2 (B), U1.6 (V+), U21.6 (V+)
/BL: C12.1, R16.2
/BR: C32.1, R36.2
/DC_IN: J50.2, SW50.3 (C)
/FM_L: J52.3, SW51.3 (C)
/FM_R: J52.5, SW51.6 (C)
/IEC_L: C8.1, R12.1, SW51.1 (A)
/IEC_R: C28.1, R32.1, SW51.4 (A)
/IN_L: RV1.2, U1.3 (+)
/IN_R: RV1.5, U21.3 (+)
/LS_L: C11.2, J54.T
/LS_R: C31.2, J54.R
/MD_L: C1.2, J51.3
/MD_R: C21.2, J51.5
/MON_L: RV1.1, SW52.2 (B)
/MON_R: RV1.4, SW52.5 (B)
/REC_L: C10.1, J53.1, SW52.1 (A)
/REC_R: C30.1, J53.4, SW52.4 (A)
/SRC_L: C9.2, SW51.2 (B)
/SRC_R: C29.2, SW51.5 (B)
/TAPE_L: J53.3, SW52.3 (C)
/TAPE_R: J53.5, SW52.6 (C)
GND: C3.2, C5.2, C6.2, C7.1, C12.2, C23.2, C25.2, C26.2, C27.1, C32.2, C50.2, C51.2, D50.1 (K), J50.1, J51.2, J52.2, J53.2, J54.S, R2.2, R5.2, R6.2, R11.2, R12.2, R14.2, R15.2, R22.2, R25.2, R26.2, R31.2, R32.2, R34.2, R35.2, RV1.3, RV1.6, U1.2 (-), U1.4 (GND), U21.2 (-), U21.4 (GND)
unnamed: C1.1, Q1.2 (B), R1.2, R2.1
unnamed: C2.1, C4.1, C5.1, C6.1, Q3.1 (C), R1.1, R3.1, R8.1, R17.2
unnamed: C2.2, R3.2, R4.1
unnamed: C3.1, R6.1, R7.2
unnamed: C4.2, R9.1
unnamed: C7.2, Q3.2 (B), R10.1
unnamed: C8.2, Q3.3 (E), R11.1
unnamed: C9.1, Q4.2 (B), R13.2, R14.1
unnamed: C10.2, Q4.3 (E), R15.1
unnamed: C11.1, R16.1, U1.5
unnamed: C21.1, Q21.2 (B), R21.2, R22.1
unnamed: C22.1, C24.1, C25.1, C26.1, Q23.1 (C), R21.1, R23.1, R28.1, R37.2
unnamed: C22.2, R23.2, R24.1
unnamed: C23.1, R26.1, R27.2
unnamed: C24.2, R29.1
unnamed: C27.2, Q23.2 (B), R30.1
unnamed: C28.2, Q23.3 (E), R31.1
unnamed: C29.1, Q24.2 (B), R33.2, R34.1
unnamed: C30.2, Q24.3 (E), R35.1
unnamed: C31.1, R36.1, U21.5
unnamed: D50.2 (A), R50.2
unnamed: Q1.1 (C), Q2.2 (B), R5.1
unnamed: Q1.3 (E), R4.2
unnamed: Q2.1 (C), R8.2, R9.2, R10.2
unnamed: Q2.3 (E), R7.1
unnamed: Q21.1 (C), Q22.2 (B), R25.1
unnamed: Q21.3 (E), R24.2
unnamed: Q22.1 (C), R28.2, R29.2, R30.2
unnamed: Q22.3 (E), R27.1

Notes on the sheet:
10.4 V
6.0
3.0
5.8
5.2
2.4
2.2
5.3

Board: 2 copper layers, 81 parts (0 on the bottom side), 52 nets, no tracks yet.

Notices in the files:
other/audio/cjss301/cjss301.sch:
(c) 2023 Carlos J. Santisteban
